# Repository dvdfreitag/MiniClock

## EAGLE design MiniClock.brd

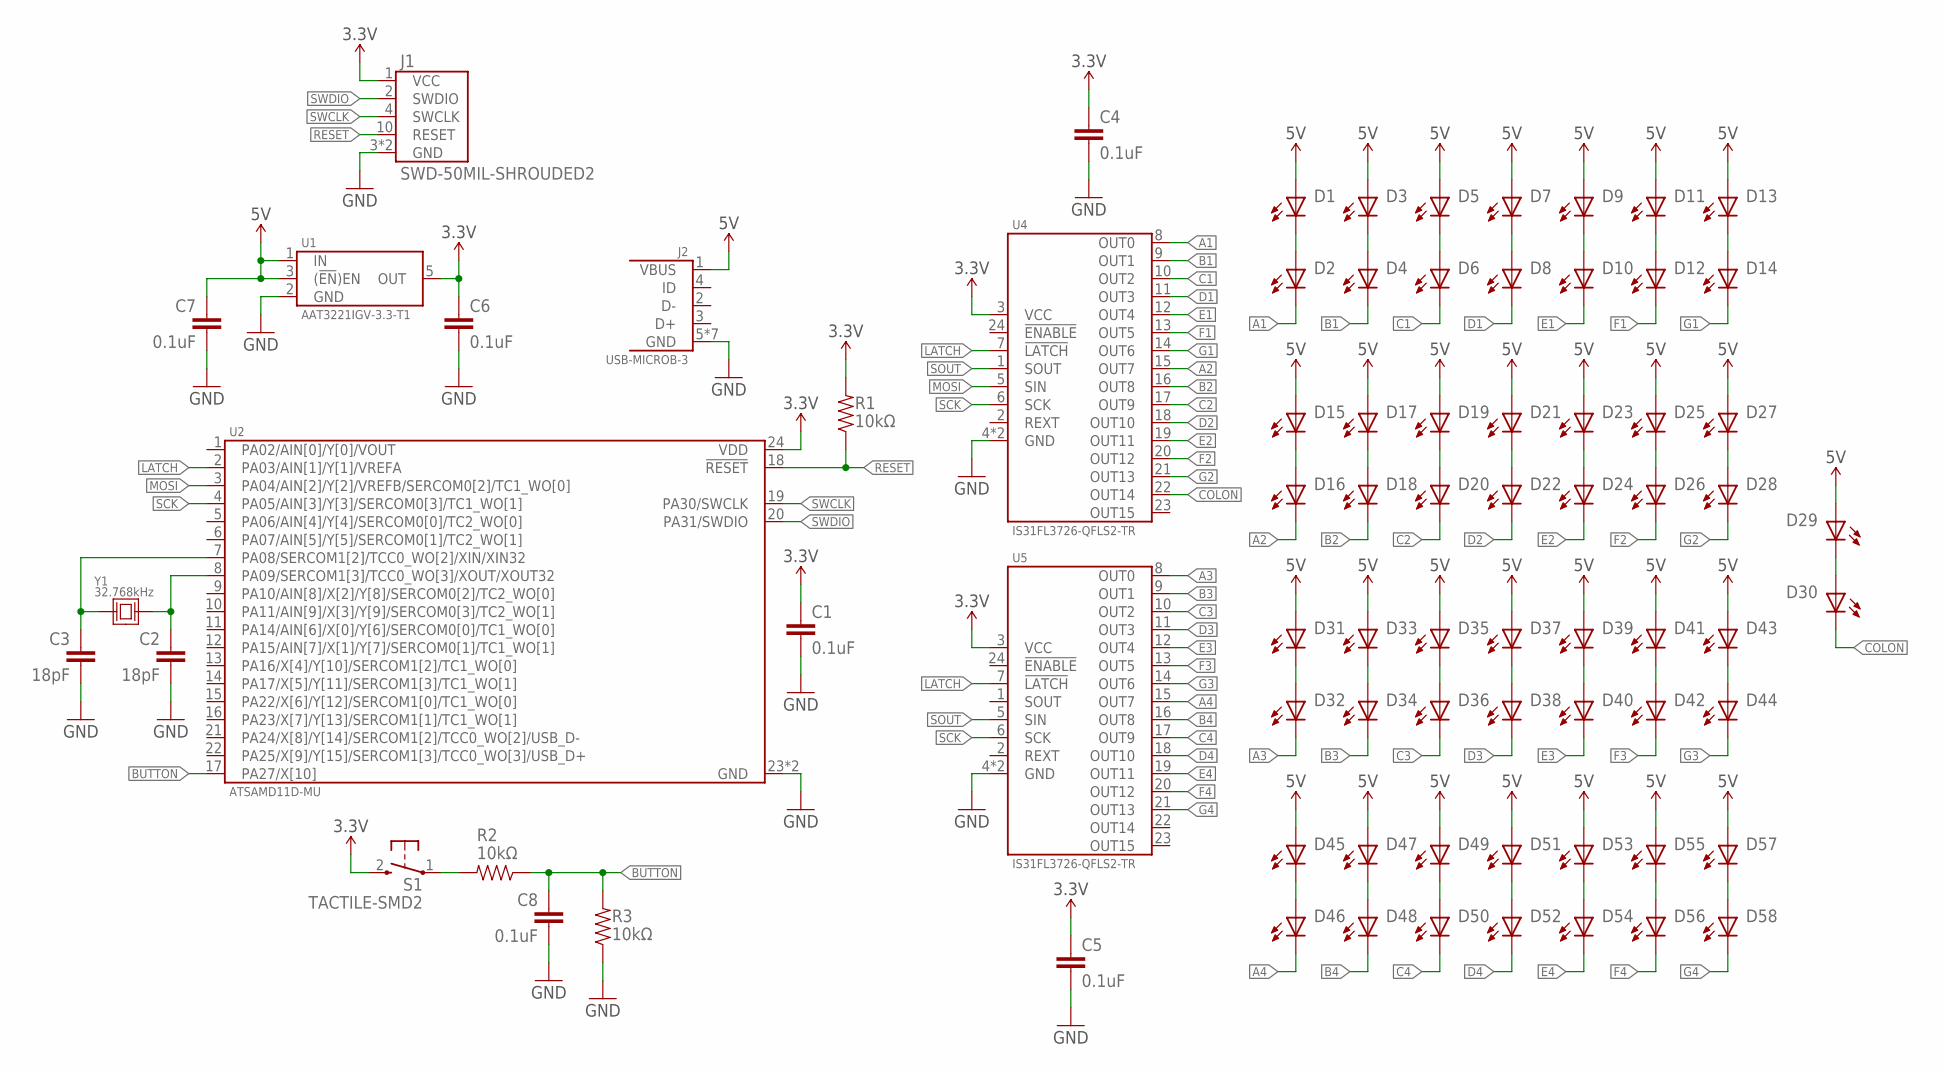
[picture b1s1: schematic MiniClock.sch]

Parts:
C1, C4, C5, C6, C7, C8: 0.1uF; 0603-CAP
C2, C3: 18pF; 0603-CAP
D1, D2, D3, D4, D5, D6, D7, D8, D9, D10, D11, D12, D13, D14, D15, D16, D17, D18, D19, D20, D21, D22, D23, D24, D25, D26, D27, D28, D29, D30, D31, D32, D33, D34, D35, D36, D37, D38, D39, D40, D41, D42, D43, D44, D45, D46, D47, D48, D49, D50, D51, D52, D53, D54, D55, D56, D57, D58: LED-0805; 0805-LED
J1: SWD-50MIL-SHROUDED2; M05X2-50MIL-SHROUD
J2: USB-MICROB-3; 10118192-0001LF
R1, R2, R3: 10kΩ; 0603-CAP
S1: TACTILE-SMD2; PTS820-J15M-SMTR-LFS
U1: AAT3221IGV-3.3-T1; SOT23-5
U2: ATSAMD11D-MU; QFN-24
U4, U5: IS31FL3726-QFLS2-TR; QFN-24-4X4
Y1: 32.768kHz; SC32S

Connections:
3.3V: C1.1, C4.1, C5.1, C6.1, J1.1 (VCC), R1.2, S1.2 (3), U1.5 (OUT), U2.24 (VDD), U4.3 (VCC), U5.3 (VCC)
5V: C7.1, D1.A, D3.A, D5.A, D7.A, D9.A, D11.A, D13.A, D15.A, D17.A, D19.A, D21.A, D23.A, D25.A, D27.A, D29.A, D31.A, D33.A, D35.A, D37.A, D39.A, D41.A, D43.A, D45.A, D47.A, D49.A, D51.A, D53.A, D55.A, D57.A, J2.1 (VBUS), U1.1 (IN), U1.3 ((!EN!)EN)
A1: D2.C, U4.8 (OUT0)
A2: D16.C, U4.15 (OUT7)
A3: D32.C, U5.8 (OUT0)
A4: D46.C, U5.15 (OUT7)
B1: D4.C, U4.9 (OUT1)
B2: D18.C, U4.16 (OUT8)
B3: D34.C, U5.9 (OUT1)
B4: D48.C, U5.16 (OUT8)
BUTTON: C8.1, R2.1, R3.2, U2.17 (PA27/X[10])
C1: D6.C, U4.10 (OUT2)
C2: D20.C, U4.17 (OUT9)
C3: D36.C, U5.10 (OUT2)
C4: D50.C, U5.17 (OUT9)
COLON: D30.C, U4.22 (OUT14)
D1: D8.C, U4.11 (OUT3)
D2: D22.C, U4.18 (OUT10)
D3: D38.C, U5.11 (OUT3)
D4: D52.C, U5.18 (OUT10)
E1: D10.C, U4.12 (OUT4)
E2: D24.C, U4.19 (OUT11)
E3: D40.C, U5.12 (OUT4)
E4: D54.C, U5.19 (OUT11)
F1: D12.C, U4.13 (OUT5)
F2: D26.C, U4.20 (OUT12)
F3: D42.C, U5.13 (OUT5)
F4: D56.C, U5.20 (OUT12)
G1: D14.C, U4.14 (OUT6)
G2: D28.C, U4.21 (OUT13)
G3: D44.C, U5.14 (OUT6)
G4: D58.C, U5.21 (OUT13)
GND: C1.2, C2.2, C3.2, C4.2, C5.2, C6.2, C7.2, C8.2, J1.3 (GND), J1.5 (GND), J2.5 (GND), J2.P$6 (GND), J2.P$7 (GND), J2.P$8 (GND), J2.P$9 (GND), J2.P$10 (GND), J2.P$11 (GND), R3.1, U1.2 (GND), U2.23 (GND), U2.P$1 (GND), U4.4 (GND), U4.PAD (GND), U5.4 (GND), U5.PAD (GND)
LATCH: U2.2 (PA03/AIN[1]/Y[1]/VREFA), U4.7 (!LATCH), U5.7 (!LATCH)
MOSI: U2.3 (PA04/AIN[2]/Y[2]/VREFB/SERCOM0[2]/TC1_W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), U4.5 (SIN)
unnamed: C2.1, U2.8 (PA09/SERCOM1[3]/TCC0_WO[3]/XOUT/XOUT32), Y1.P$2 (2)
unnamed: C3.1, U2.7 (PA08/SERCOM1[2]/TCC0_WO[2]/XIN/XIN32), Y1.P$1 (1)
unnamed: D1.C, D2.A
unnamed: D13.C, D14.A
unnamed: D11.C, D12.A
unnamed: D9.C, D10.A
unnamed: D7.C, D8.A
unnamed: D5.C, D6.A
unnamed: D3.C, D4.A
unnamed: D27.C, D28.A
unnamed: D25.C, D26.A
unnamed: D23.C, D24.A
unnamed: D15.C, D16.A
unnamed: D17.C, D18.A
unnamed: D19.C, D20.A
unnamed: D21.C, D22.A
unnamed: D29.C, D30.A
unnamed: D31.C, D32.A
unnamed: D43.C, D44.A
unnamed: D41.C, D42.A
unnamed: D39.C, D40.A
unnamed: D37.C, D38.A
unnamed: D35.C, D36.A
unnamed: D33.C, D34.A
unnamed: D45.C, D46.A
unnamed: D47.C, D48.A
unnamed: D49.C, D50.A
unnamed: D51.C, D52.A
unnamed: D53.C, D54.A
unnamed: D55.C, D56.A
unnamed: D57.C, D58.A
unnamed: R2.2, S1.1
RESET: J1.10 (RESET), R1.1, U2.18 (!RESET)
SCK: U2.4 (PA05/AIN[3]/Y[3]/SERCOM0[3]/TC1_WO[1]), U4.6 (SCK), U5.6 (SCK)
SOUT: U4.1 (SOUT), U5.5 (SIN)
SWCLK: J1.4 (SWCLK), U2.19 (PA30/SWCLK)
SWDIO: J1.2 (SWDIO), U2.20 (PA31/SWDIO)

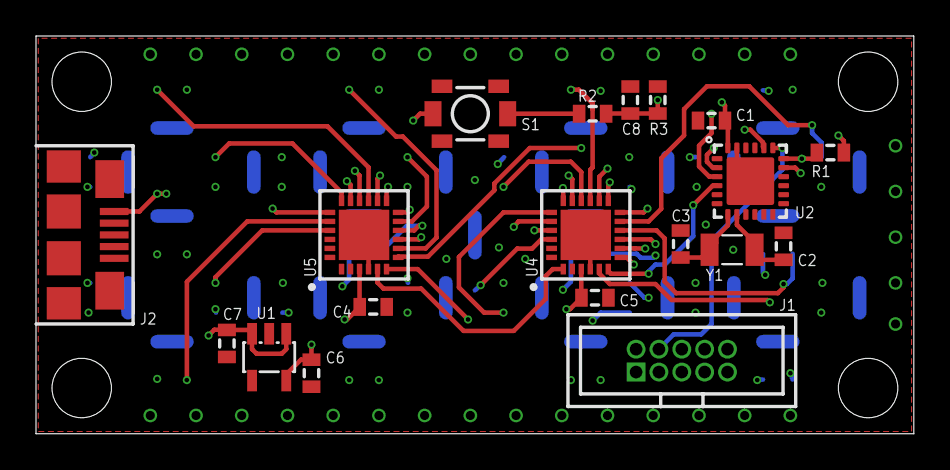
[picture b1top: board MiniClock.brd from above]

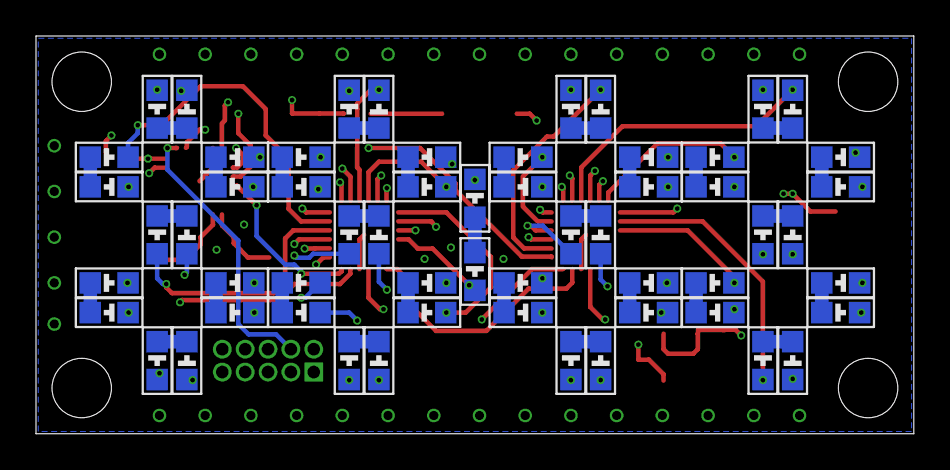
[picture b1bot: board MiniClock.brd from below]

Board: 4 copper layers, 48.8 x 22.1 mm, 77 parts (58 on the bottom side), 72 nets.

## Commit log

2016-08-11 Create LICENSE
